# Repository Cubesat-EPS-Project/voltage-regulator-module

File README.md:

# voltage-regulator-module
Work in progress on main branch

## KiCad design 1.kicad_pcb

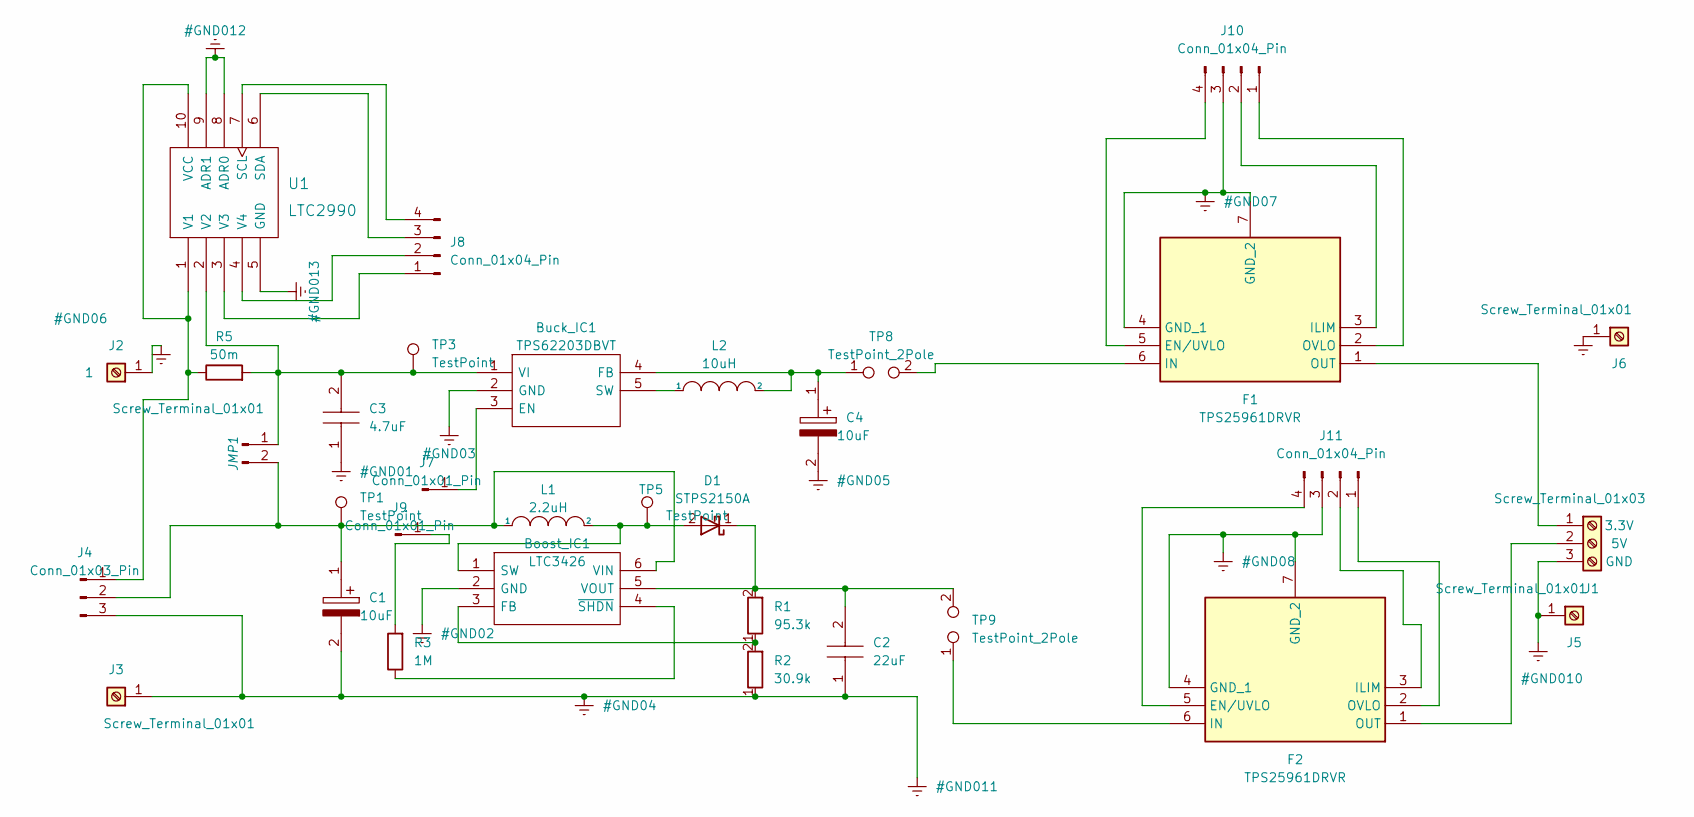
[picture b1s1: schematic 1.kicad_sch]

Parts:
Boost_IC1: LTC3426; SOT95P280X90-6N; Mouser Part Number 584-LTC3426ES6TRMPBF
Buck_IC1: TPS62203DBVT; SOT95P280X145-5N; Mouser Part Number 595-TPS62203DBVT
C1, C4: 10uF; CAPC2012X94N; Mouser Part Number 598-AFK106M35C12T-F
C2: 22uF; C3216_Commercial; Mouser Part Number 81-ZRB18AR61A226ME1L
C3: 4.7uF; C1210; Mouser Part Number 80-C1210C475K4RAUTO
D1: STPS2150A; DIOM5126X265N
F1, F2: TPS25961DRVR; SON65P200X200X80-7N; Mouser Part Number 595-TPS25961DRVR
J1: Screw_Terminal_01x03; TerminalBlock_Phoenix_MKDS-1,5-3_1x03_P5.00mm_Horizontal
J2, J3, J5, J6: Screw_Terminal_01x01; Pin_D1.3mm_L11.0mm_LooseFit
J4: Conn_01x03_Pin; TerminalBlock_Phoenix_MKDS-1,5-3_1x03_P5.00mm_Horizontal
J7, J9: Conn_01x01_Pin; PinHeader_1x01_P2.54mm_Vertical
J8, J10, J11: Conn_01x04_Pin; PinHeader_1x04_P2.54mm_Vertical
JMP1: EN; PinHeader_1x02_P2.54mm_Vertical
L1: 2.2uH; IHLP2020CZER2R2M8A
L2: 10uH; SRN1060-100M
R1: 95.3k; RESC2012X60N
R2: 30.9k; RC0603FR-0730K9L
R3: 1M; RESC1608X55N
R5: 50m; RESC3216X88N
TP1, TP3, TP5: TestPoint; TestPoint_THTPad_1.5x1.5mm_Drill0.7mm
TP8, TP9: TestPoint_2Pole; TestPoint_2Pads_Pitch2.54mm_Drill0.8mm
U1: LTC2990; SOP50P490X110-10N

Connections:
Earth: Boost_IC1.2 (GND), Buck_IC1.2 (GND), C1.2, C2.1, C3.1, C4.2, F1.4 (GND_1), F1.7 (GND_2), F2.4 (GND_1), F2.7 (GND_2), J1.3, J2.1, J3.1, J4.3, J5.1, J6.1, J10.3, J11.3, R2.1, U1.5 (GND), U1.8 (ADR0), U1.9 (ADR1)
unnamed: Boost_IC1.3 (FB), R1.1, R2.2
unnamed: Boost_IC1.1 (SW), D1.2 (A), L1.2, TP5.1
unnamed: Boost_IC1.6 (VIN), C1.1, J4.2, JMP1.2, L1.1, TP1.1
unnamed: Boost_IC1.5 (VOUT), C2.2, D1.1 (K), R1.2, TP9.2
unnamed: Boost_IC1.4 (~SHDN), R3.1
unnamed: Buck_IC1.3 (EN), J7.1
unnamed: Buck_IC1.4 (FB), C4.1, L2.2, TP8.1
unnamed: Buck_IC1.5 (SW), L2.1
unnamed: Buck_IC1.1 (VI), C3.2, JMP1.1, R5.2, TP3.1, U1.2 (V2)
unnamed: F1.5 (EN/UVLO), J10.4
unnamed: F1.3 (ILIM), J10.2
unnamed: F1.6 (IN), TP8.2
unnamed: F1.1 (OUT), J1.1
unnamed: F1.2 (OVLO), J10.1
unnamed: F2.5 (EN/UVLO), J11.4
unnamed: F2.3 (ILIM), J11.2
unnamed: F2.6 (IN), TP9.1
unnamed: F2.1 (OUT), J1.2
unnamed: F2.2 (OVLO), J11.1
unnamed: J4.1, R5.1, U1.1 (V1), U1.10 (VCC)
unnamed: J8.1, U1.3 (V3)
unnamed: J8.2, U1.4 (V4)
unnamed: J8.3, U1.6 (SDA)
unnamed: J8.4, U1.7 (SCL)
unnamed: J9.1, R3.2

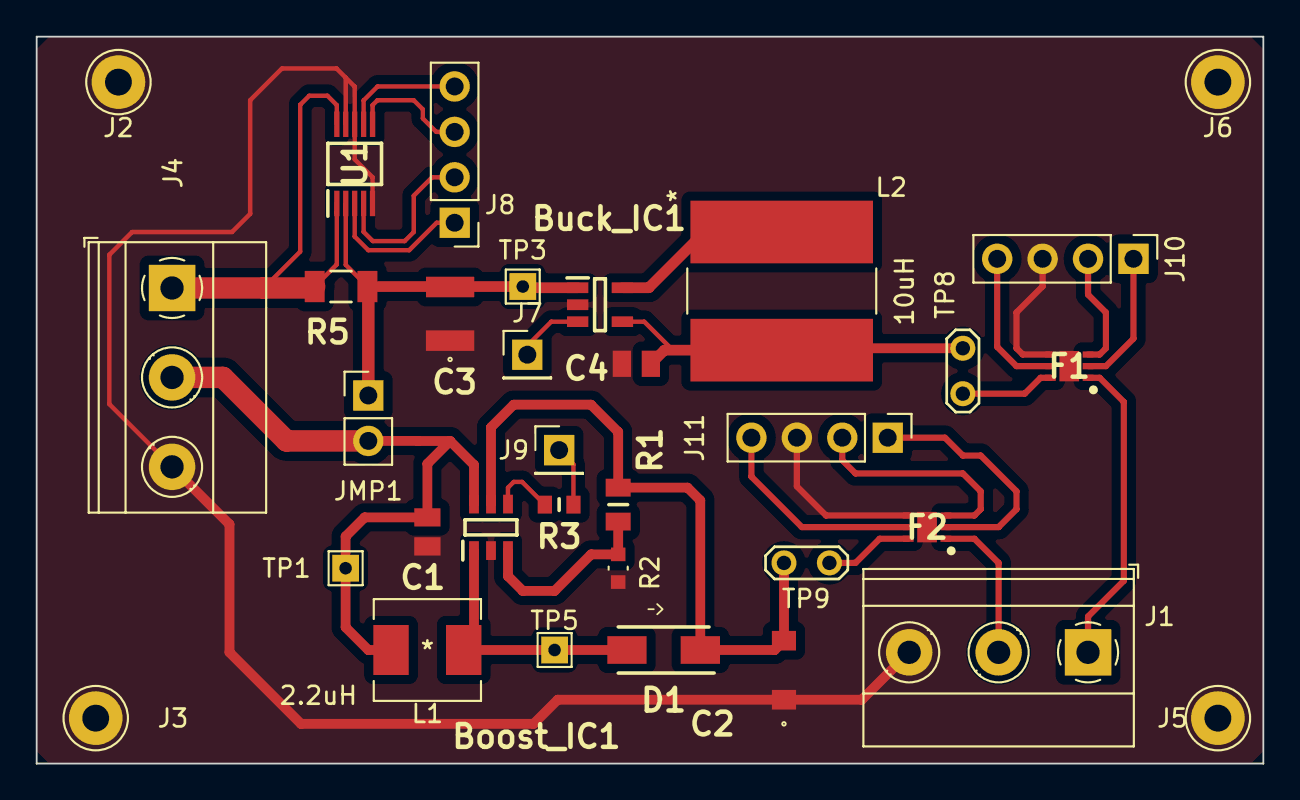
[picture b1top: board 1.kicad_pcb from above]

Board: 2 copper layers, 68.6 x 40.6 mm, 33 parts (0 on the bottom side), 26 nets.

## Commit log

2023-01-30 INIT1
2023-01-30 INIT2
2023-01-30 Patch
2023-02-01 Fixes + Patches
2023-02-03 Replaced Al elec caps
2023-02-10 Fixed routing issues and naming of pins
2023-02-10 FInal...I guess
2023-02-13 Update Gerbuhs
2023-03-01 sch edits
2023-03-27 Start redesign coz boost circuit is f'd up
2023-03-29 Almost there
2023-03-30 Define edge cuts
2023-04-03 Fixes
2023-05-08 update plots
2023-05-30 Add protection circ

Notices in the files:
parts and their libraries:
Copyright 2021 Accelerated Designs. All rights reserved.
